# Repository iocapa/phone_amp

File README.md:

# phone_amp
Headphones amplifier/splitter for RJ9 handset phones.

Used "on the cable" for adding amplified headset support to standard RJ9 handset telephones.

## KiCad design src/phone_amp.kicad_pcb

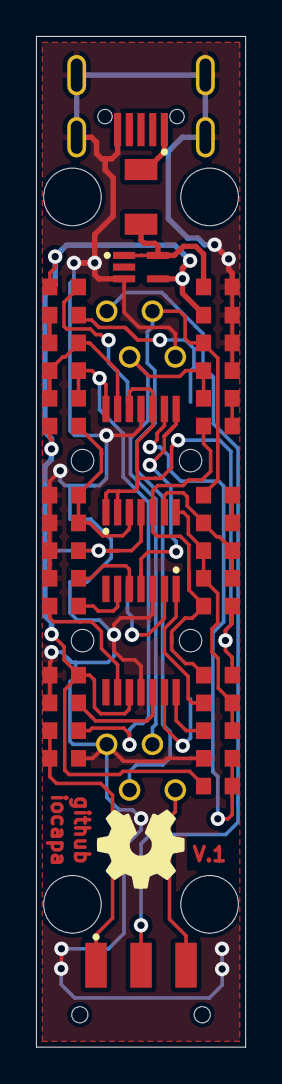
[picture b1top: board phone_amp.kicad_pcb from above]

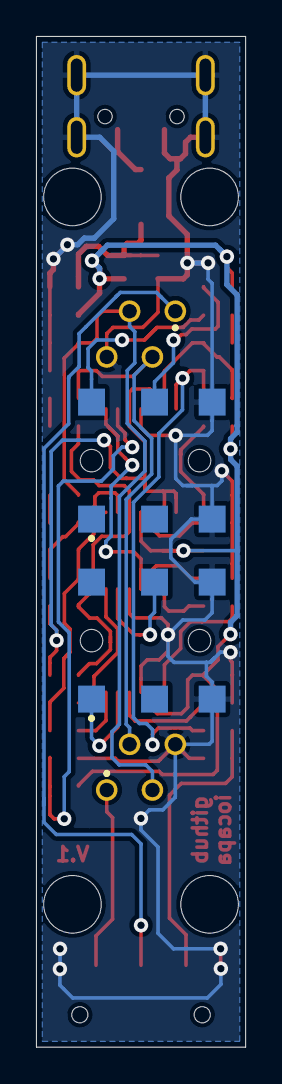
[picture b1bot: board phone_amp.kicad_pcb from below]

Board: 2 copper layers, 11.6 x 56.1 mm, 41 parts (4 on the bottom side), 31 nets.

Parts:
C1, C6, C7, C8: 220n; CHIP-0603-NO-SILK
C2, C4, C9, C13: 22n; CHIP-0603-NO-SILK
C3, C10, C11, C12, C14, C15, C16: 1u; CHIP-0603-NO-SILK
C5: 2.2n; CHIP-0603-NO-SILK
F1: 200mA; FUSE-1206-NO-SILK
J1: M_USB_B; USB-MICRO-TH-NO-SILK
J2, J3: PJ313D; JACK-3.5MM-NO-SILK
J4, J5: RJ9_4P4C; RJ9-4P4C-NO-SILK
R1: 27.3k; CHIP-0603-NO-SILK
R2, R6, R7, R9, R10: 2.4k; CHIP-0603-NO-SILK
R3, R4, R5: 18k; CHIP-0603-NO-SILK
R8: 4.3k; CHIP-0603-NO-SILK
R11, R13, R14: 100k; CHIP-0603-NO-SILK
R12: 43k; CHIP-0603-NO-SILK
R15: 2.2k; CHIP-0603-NO-SILK
SW1: SWITCH_INV; SWITCH-SPDT-NO-SILK
U1: TPA6139A2; TSSOP-14-NO-SILK
U2: MCP6024; TSSOP-14-NO-SILK
U3: TC1017; SC-70-NO-SILK

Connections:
+3V3: C11.2, C15.2, C16.2, R11.1, R13.1, R15.2, U1.10, U2.4, U3.4
GND: C10.1, C11.1, C12.1, C14.2, C15.1, C16.1, J1.5, J1.6, J1.7, J1.8, J1.9, J2.3, J2.4, J3.3, J3.4, J4.4, J5.4, R1.2, R3.2, R4.2, R8.1, R12.2, R14.2, U1.3, U1.11, U2.11, U3.3
HP_MIC: C1.2, J2.6
HP_MIC_BIAS: J2.5, R15.1
HP_MIC_OUT: C8.1, R8.2, SW1.1
HP_MUTE: U1.4, U2.8
HP_SPK_L: J3.5, U1.2
HP_SPK_PRE: C2.2, C4.2, C13.1, R10.1, U2.7
HP_SPK_R: J3.1, U1.13
HS_MIC_P: J4.1, SW1.3
HS_SPK_N: C6.2, J4.3, J5.3, R4.1
HS_SPK_P: C7.2, J4.2, J5.2, R3.1
unnamed: C1.1, R2.2
unnamed: C2.1, U1.14
unnamed: C3.1, U1.6
unnamed: C3.2, U1.9
unnamed: C4.1, U1.1
unnamed: C5.1, C8.2, R5.1, U2.14
unnamed: C5.2, R2.1, R5.2, U2.13
unnamed: C6.1, R6.2
unnamed: C7.1, R7.2
unnamed: C9.1, R7.1, R9.2, U2.5
unnamed: C10.2, U1.5
unnamed: C12.2, F1.2, U3.1, U3.5
unnamed: C13.2, R6.1, R10.2, U2.6
unnamed: C14.1, R13.2, R14.1, U2.3
unnamed: F1.1, J1.1
unnamed: R1.1, U1.12
unnamed: R11.2, R12.1, U2.9
PHONE_MIC_P: J5.1, SW1.2
VGND: C9.2, R9.1, U2.1, U2.2, U2.10, U2.12

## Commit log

2015-05-01 Added footprints for some components
2015-05-01 Added switch datasheet
2015-05-06 added micro USB connector footprint and modified schematic for new symbol.
2015-05-06 Initial revision
2015-05-08 Added some footprints.
2015-05-09 Added initial pcb.
2015-05-09 Placed fuse.
2015-05-18 Updated schematic
2015-05-18 Updated schematic and related files.
2015-05-19 Made modifications to pcb.
2015-05-19 Made some pcb changes.
2015-05-20 Updated PCB.
2015-05-22 Uploaded finished design.
2015-05-23 Sent to production.
2015-06-30 Tested. Ready for small batches
2015-06-30 Added component placement map
2016-03-19 Added library subproject.
2016-03-19 Removed standalone lib folder.:
2016-03-19 Made some cleaning
2016-03-19 Submodule moved in lib folder
2016-03-19 Modified lib path.
